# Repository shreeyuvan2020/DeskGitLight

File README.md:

# DeskGitLight
A PCB in the shape of the GitHub cat that lights up more as it becomes darker!
## BOM:
- 1x Battery Holder
- 2x Potentiometer
- 2x LED
- 1x Photoresistor
- 2x NPN Transistor
- 2x 910 ohm resistor
- 2x 220 Ohm resistor
## Schematic:

## PCB:

## Features:
- Orpheus AND git silkscreen art!
- The ears of the github cat light up!
- Perfectly traced outline of the github cat(at least that's what I think)
- 5V Battery
- Compact PCB loaded with components and silkscreen art

Made as a part of solder.hackclub.com :D

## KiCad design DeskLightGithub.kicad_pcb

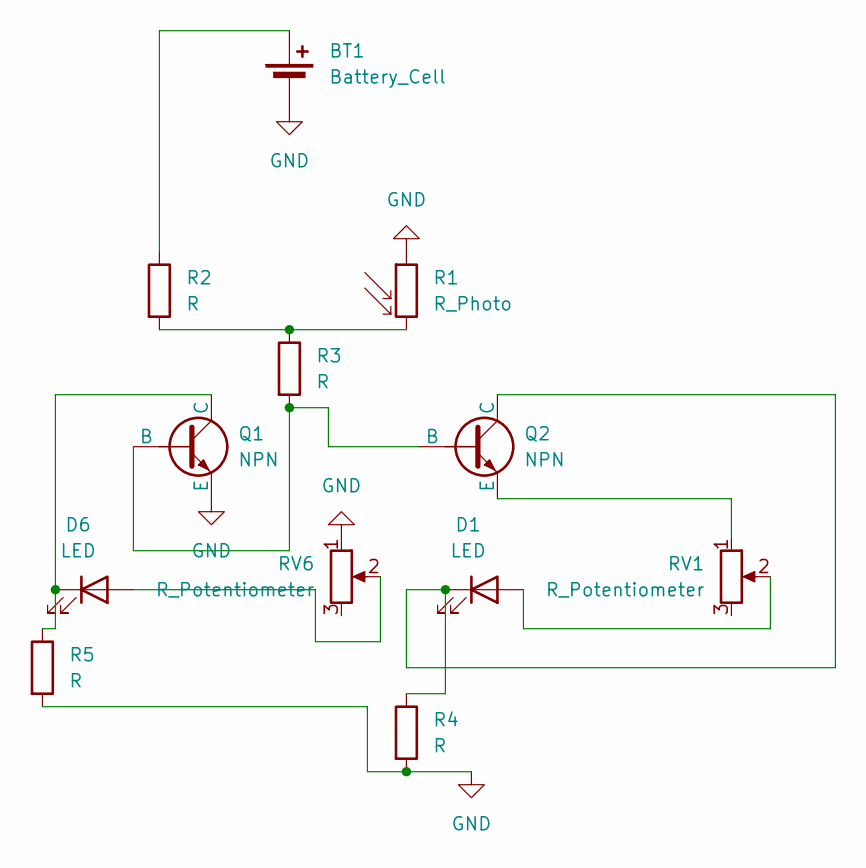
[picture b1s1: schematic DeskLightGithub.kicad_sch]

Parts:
BT1: Battery_Cell; BatteryHolder_Keystone_3034_1x20mm
D1, D6: LED; LED_D5.0mm
Q1, Q2: NPN; TO-92L_HandSolder
R1: R_Photo; R_LDR_5.1x4.3mm_P3.4mm_Vertical
R2, R3, R4, R5: R; R_Axial_DIN0207_L6.3mm_D2.5mm_P7.62mm_Horizontal
RV1, RV6: R_Potentiometer; Potentiometer_Vishay_T73YP_Vertical

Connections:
GND: BT1.2 (-), Q1.3 (E), R1.1, R4.2, R5.2, RV6.1
unnamed: BT1.1 (+), R2.1
unnamed: D1.2 (A), RV1.2
unnamed: D1.1 (K), Q2.1 (C), R4.1
unnamed: D6.2 (A), RV6.2
unnamed: D6.1 (K), Q1.1 (C), R5.1
unnamed: Q1.2 (B), Q2.2 (B), R3.2
unnamed: Q2.3 (E), RV1.1
unnamed: R1.2, R2.2, R3.1

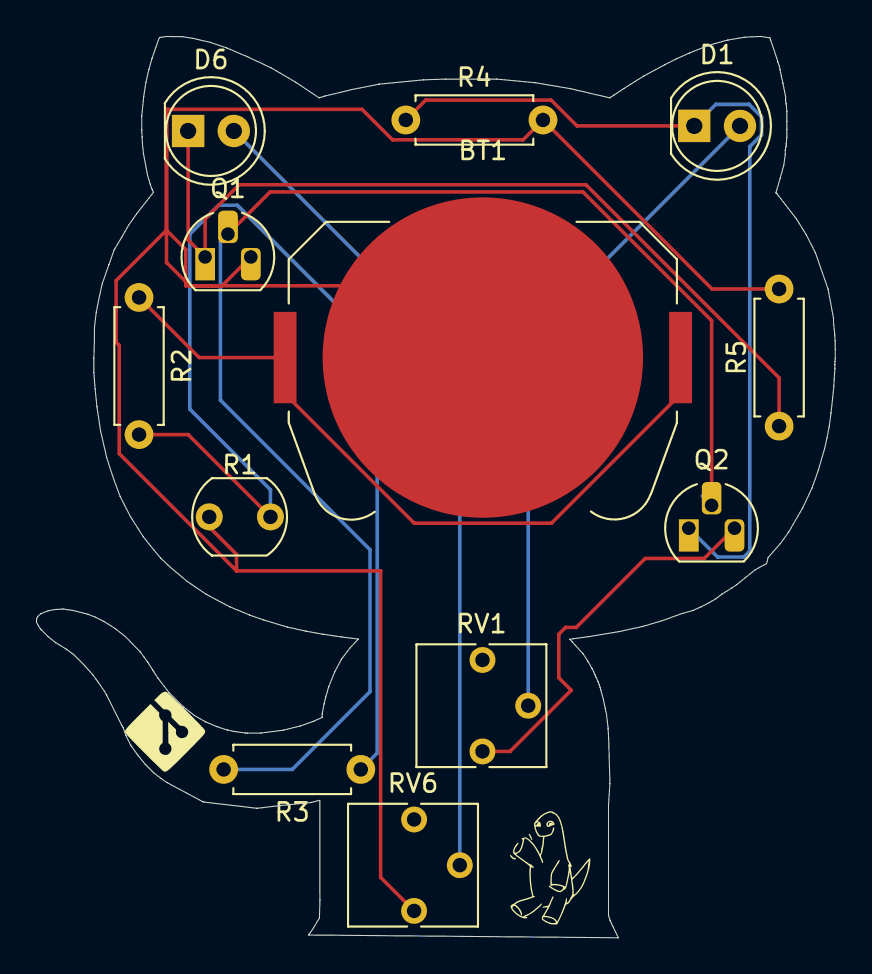
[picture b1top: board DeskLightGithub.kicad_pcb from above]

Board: 2 copper layers, 44.4 x 50.1 mm, 12 parts (0 on the bottom side), 9 nets.

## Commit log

2025-06-12 Added production files
2025-06-12 Add PCB files
